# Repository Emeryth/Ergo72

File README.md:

# Ergo72

A redesigned ErgoDox keyboard PCB.
Check out [https://emeryth.net/ergo72-keyboard/](https://emeryth.net/ergo72-keyboard/) for more info.

Design features:

* Same key layout as the original Ergodox
* STM32 microcontroller (STM32F072)
* MCU in both halves allowing independent operation
* USB-C
* All components on PCB, no modules
* Extension header for OLED screen or anything else
* Single PCB for both hands
* QMK firmware supported

Basic acrylic case design included.

QMK firmware: [https://github.com/Emeryth/qmk_firmware/tree/ergo72](https://github.com/Emeryth/qmk_firmware/tree/ergo72)

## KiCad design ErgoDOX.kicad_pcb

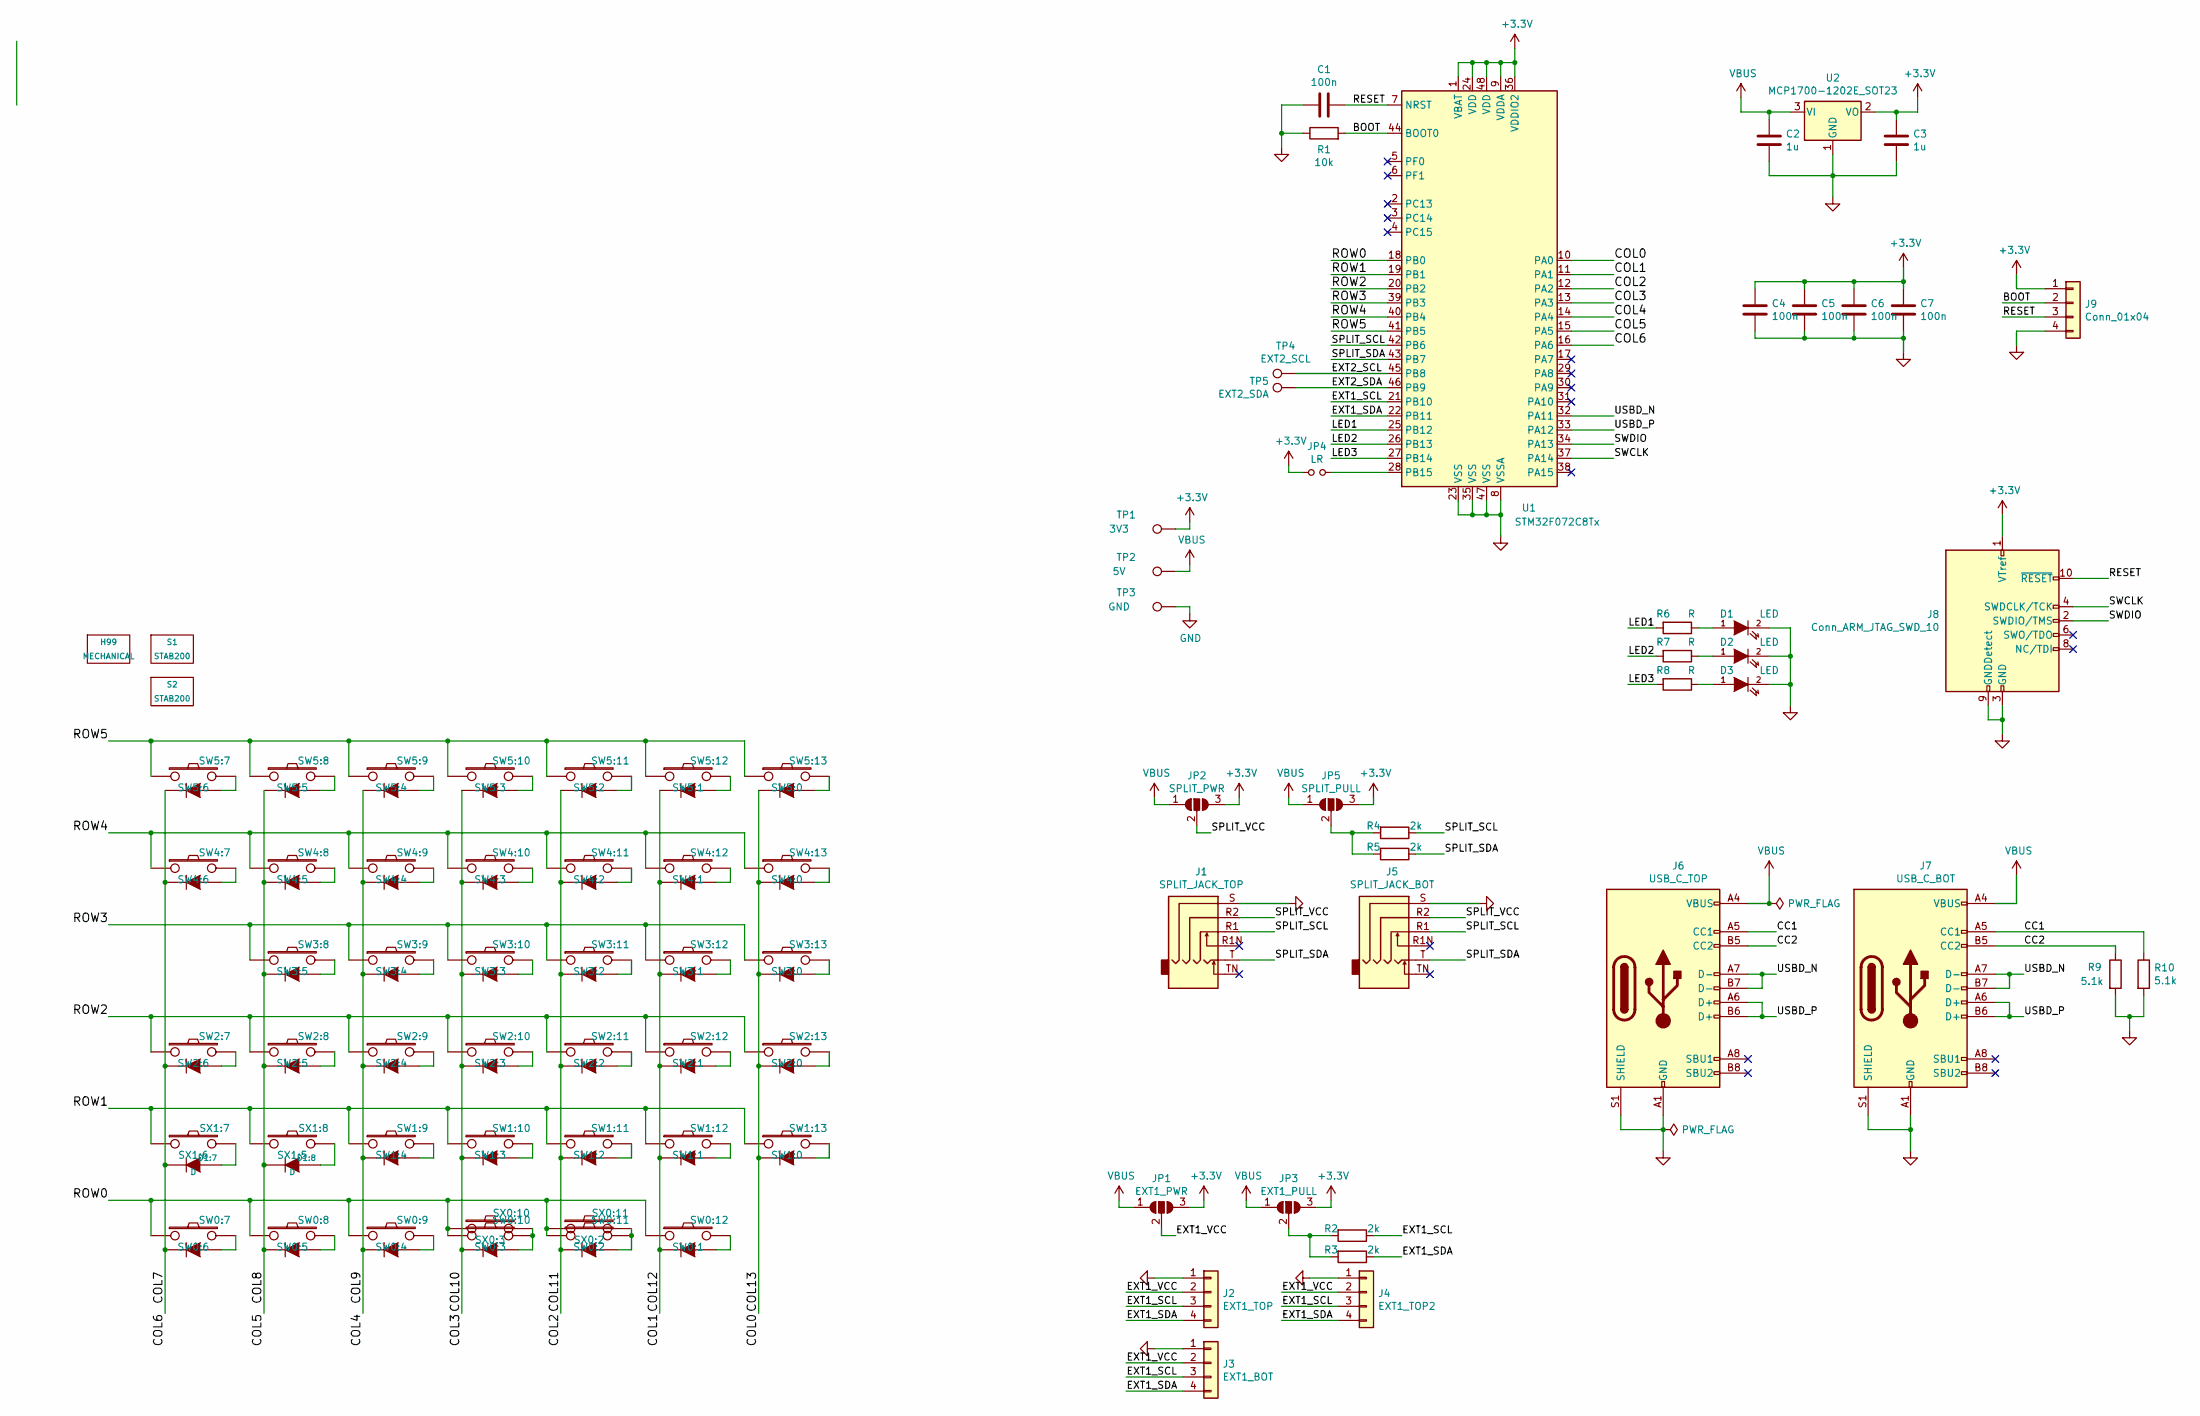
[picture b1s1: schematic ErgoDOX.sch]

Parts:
C1, C4, C5, C6, C7: 100n; C_0603_1608Metric
C2, C3: 1u; C_0805_2012Metric
D1, D2, D3: LED; LED_0603_1608Metric
D1:7, D1:8: D; DIODE
H99: MECHANICAL; ErgoDOXmech
J1: SPLIT_JACK_TOP; Jack_3.5mm_PJ31060-I_Horizontal
J2: EXT1_TOP; PinHeader_1x04_P2.54mm_Vertical
J3: EXT1_BOT; PinHeader_1x04_P2.54mm_Vertical
J4: EXT1_TOP2; Molex_PicoBlade_53047-0410_1x04_P1.25mm_Vertical
J5: SPLIT_JACK_BOT; Jack_3.5mm_PJ31060-I_Horizontal
J6: USB_C_TOP; USB_C_Receptacle_XKB_U262-16XN-4BVC11
J7: USB_C_BOT; USB_C_Receptacle_XKB_U262-16XN-4BVC11
J8: Conn_ARM_JTAG_SWD_10; PinHeader_2x05_P1.27mm_Vertical_SMD
J9: Conn_01x04; PinHeader_1x04_P2.54mm_Horizontal
JP1: EXT1_PWR; SolderJumper-3_P2.0mm_Open_TrianglePad1.0x1.5mm
JP2: SPLIT_PWR; SolderJumper-3_P2.0mm_Open_TrianglePad1.0x1.5mm
JP3: EXT1_PULL; SolderJumper-3_P2.0mm_Open_TrianglePad1.0x1.5mm
JP4: LR; SolderJumper-2_P1.3mm_Open_TrianglePad1.0x1.5mm
JP5: SPLIT_PULL; SolderJumper-3_P2.0mm_Open_TrianglePad1.0x1.5mm
R1: 10k; R_0603_1608Metric
R2, R3, R4, R5: 2k; R_0603_1608Metric
R6, R7, R8: R; R_0603_1608Metric
R9, R10: 5.1k; R_0603_1608Metric
S1, S2: STAB200
SW0:7: SW0:6; MX_FLIP_DIODE
SW0:8: SW0:5; MX_FLIP_DIODE
SW0:9: SW0:4; MX_FLIP_DIODE
SW0:10: SW0:3; MX_FLIP_DIODE
SW0:11: SW0:2; MX_FLIP_DIODE
SW0:12: SW0:1; MX_FLIP_DIODE
SW1:9: SW1:4; MX_FLIP_DIODE
SW1:10: SW1:3; MX_FLIP_DIODE
SW1:11: SW1:2; MX_FLIP_DIODE
SW1:12: SW1:1; MX_FLIP_DIODE
SW1:13: SW1:0; MX_FLIP_DIODE
SW2:7: SW2:6; MX_FLIP_DIODE
SW2:8: SW2:5; MX_FLIP_DIODE
SW2:9: SW2:4; MX_FLIP_DIODE
SW2:10: SW2:3; MX_FLIP_DIODE
SW2:11: SW2:2; MX_FLIP_DIODE
SW2:12: SW2:1; MX_FLIP_DIODE
SW2:13: SW2:0; MX_FLIP_XX
SW3:8: SW3:5; MX_FLIP_DIODE
SW3:9: SW3:4; MX_FLIP_DIODE
SW3:10: SW3:3; MX_FLIP_DIODE
SW3:11: SW3:2; MX_FLIP_DIODE
SW3:12: SW3:1; MX_FLIP_DIODE
SW3:13: SW3:0; MX_FLIP_XX
SW4:7: SW4:6; MX_FLIP_DIODE
SW4:8: SW4:5; MX_FLIP_DIODE
SW4:9: SW4:4; MX_FLIP_DIODE
SW4:10: SW4:3; MX_FLIP_DIODE
SW4:11: SW4:2; MX_FLIP_DIODE
SW4:12: SW4:1; MX_FLIP_DIODE
SW4:13: SW4:0; MX_FLIP_XX
SW5:7: SW5:6; MX_FLIP_DIODE
SW5:8: SW5:5; MX_FLIP_DIODE
SW5:9: SW5:4; MX_FLIP_DIODE
SW5:10: SW5:3; MX_FLIP_DIODE
SW5:11: SW5:2; MX_FLIP_DIODE
SW5:12: SW5:1; MX_FLIP_DIODE
SW5:13: SW5:0; MX_FLIP_XX
SX0:10: SX0:3; MX_FLIP
SX0:11: SX0:2; MX_FLIP
SX1:7: SX1:6; MX_FLIP
SX1:8: SX1:5; MX_FLIP
TP1: 3V3; TestPoint_Pad_D1.5mm
TP2: 5V; TestPoint_Pad_D1.5mm
TP3: GND; TestPoint_Pad_D1.5mm
TP4: EXT2_SCL; TestPoint_Pad_D1.5mm
TP5: EXT2_SDA; TestPoint_Pad_D1.5mm
U1: STM32F072C8Tx; LQFP-48_7x7mm_P0.5mm
U2: MCP1700-1202E_SOT23; SOT-23

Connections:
+3V3: C3.1, C4.1, C5.1, C6.1, C7.1, J8.1 (VTref), J9.1, JP1.3 (B), JP2.3 (B), JP3.3 (B), JP4.1, JP5.3 (B), TP1.1, U1.1 (VBAT), U1.9 (VDDA), U1.24 (VDD), U1.36 (VDDIO2), U1.48 (VDD), U2.2 (VO)
/BOOT: J9.2, R1.2, U1.44 (BOOT0)
/CC1: J6.A5 (CC1), J7.A5 (CC1), R10.1
/CC2: J6.B5 (CC2), J7.B5 (CC2), R9.1
/COL0: SW1:13.4 (K), SW2:13.4 (K), SW3:13.4 (K), SW4:13.4 (K), SW5:13.4 (K), U1.10 (PA0)
/COL1: SW0:12.4 (K), SW1:12.4 (K), SW2:12.4 (K), SW3:12.4 (K), SW4:12.4 (K), SW5:12.4 (K), U1.11 (PA1)
/COL4: SW0:9.4 (K), SW1:9.4 (K), SW2:9.4 (K), SW3:9.4 (K), SW4:9.4 (K), SW5:9.4 (K), U1.14 (PA4)
/COL5: D1:8.2 (K), SW0:8.4 (K), SW2:8.4 (K), SW3:8.4 (K), SW4:8.4 (K), SW5:8.4 (K), U1.15 (PA5)
/COL6: D1:7.2 (K), SW0:7.4 (K), SW2:7.4 (K), SW4:7.4 (K), SW5:7.4 (K), U1.16 (PA6)
/COL10: SW0:10.4 (K), SW1:10.4 (K), SW2:10.4 (K), SW3:10.4 (K), SW4:10.4 (K), SW5:10.4 (K), U1.13 (PA3)
/COL11: SW0:11.4 (K), SW1:11.4 (K), SW2:11.4 (K), SW3:11.4 (K), SW4:11.4 (K), SW5:11.4 (K), U1.12 (PA2)
/EXT1_SCL: J2.3, J3.3, J4.3, R2.1, U1.21 (PB10)
/EXT1_SDA: J2.4, J3.4, J4.4, R3.1, U1.22 (PB11)
/EXT1_VCC: J2.2, J3.2, J4.2, JP1.2 (C)
/EXT2_SCL: TP4.1, U1.45 (PB8)
/EXT2_SDA: TP5.1, U1.46 (PB9)
/LED1: R6.2, U1.25 (PB12)
/LED2: R7.2, U1.26 (PB13)
/LED3: R8.2, U1.27 (PB14)
/RESET: C1.1, J8.10 (~RESET~), J9.3, U1.7 (NRST)
/ROW0: SW0:7.1, SW0:8.1, SW0:9.1, SW0:10.1, SW0:11.1, SW0:12.1, SX0:10.1, SX0:11.1, U1.18 (PB0)
/ROW1: SW1:9.1, SW1:10.1, SW1:11.1, SW1:12.1, SW1:13.1, SX1:7.1, SX1:8.1, U1.19 (PB1)
/ROW2: SW2:7.1, SW2:8.1, SW2:9.1, SW2:10.1, SW2:11.1, SW2:12.1, SW2:13.1, U1.20 (PB2)
/ROW3: SW3:8.1, SW3:9.1, SW3:10.1, SW3:11.1, SW3:12.1, SW3:13.1, U1.39 (PB3)
/ROW4: SW4:7.1, SW4:8.1, SW4:9.1, SW4:10.1, SW4:11.1, SW4:12.1, SW4:13.1, U1.40 (PB4)
/ROW5: SW5:7.1, SW5:8.1, SW5:9.1, SW5:10.1, SW5:11.1, SW5:12.1, SW5:13.1, U1.41 (PB5)
/SPLIT_SCL: J1.R1, J5.R1, R4.1, U1.42 (PB6)
/SPLIT_SDA: J1.T, J5.T, R5.1, U1.43 (PB7)
/SPLIT_VCC: J1.R2, J5.R2, JP2.2 (C)
/SWCLK: J8.4 (SWDCLK/TCK), U1.37 (PA14)
/SWDIO: J8.2 (SWDIO/TMS), U1.34 (PA13)
/USBD_N: J6.A7 (D-), J6.B7 (D-), J7.A7 (D-), J7.B7 (D-), U1.32 (PA11)
/USBD_P: J6.A6 (D+), J6.B6 (D+), J7.A6 (D+), J7.B6 (D+), U1.33 (PA12)
GND: C1.2, C2.2, C3.2, C4.2, C5.2, C6.2, C7.2, D1.2 (K), D2.2 (K), D3.2 (K), J1.S, J2.1, J3.1, J4.1, J5.S, J6.A1 (GND), J6.A12 (GND), J6.B1 (GND), J6.B12 (GND), J6.S1 (SHIELD), J7.A1 (GND), J7.A12 (GND), J7.B1 (GND), J7.B12 (GND), J7.S1 (SHIELD), J8.3 (GND), J8.5 (GND), J8.9 (GNDDetect), J9.4, R1.1, R9.2, R10.2, TP3.1, U1.8 (VSSA), U1.23 (VSS), U1.35 (VSS), U1.47 (VSS), U2.1 (GND); also elsewhere on the board
unnamed: D1.1 (A), R6.1
unnamed: D1:7.1 (A), SX1:7.2
unnamed: D1:8.1 (A), SX1:8.2
unnamed: D2.1 (A), R7.1
unnamed: D3.1 (A), R8.1
unnamed: JP3.2 (C), R2.2, R3.2
unnamed: JP4.2, U1.28 (PB15)
unnamed: JP5.2 (C), R4.2, R5.2
unnamed: SW0:7.2, SW0:7.3 (A)
unnamed: SW0:8.2, SW0:8.3 (A)
unnamed: SW0:9.2, SW0:9.3 (A)
unnamed: SW0:10.2, SW0:10.3 (A), SX0:10.2
unnamed: SW0:11.2, SW0:11.3 (A), SX0:11.2
unnamed: SW0:12.2, SW0:12.3 (A)
unnamed: SW1:9.2, SW1:9.3 (A)
unnamed: SW1:10.2, SW1:10.3 (A)
unnamed: SW1:11.2, SW1:11.3 (A)
unnamed: SW1:12.2, SW1:12.3 (A)
unnamed: SW1:13.2, SW1:13.3 (A)
unnamed: SW2:7.2, SW2:7.3 (A)
unnamed: SW2:8.2, SW2:8.3 (A)
unnamed: SW2:9.2, SW2:9.3 (A)
unnamed: SW2:10.2, SW2:10.3 (A)
unnamed: SW2:11.2, SW2:11.3 (A)
unnamed: SW2:12.2, SW2:12.3 (A)
unnamed: SW2:13.2, SW2:13.3 (A)
unnamed: SW3:8.2, SW3:8.3 (A)
unnamed: SW3:9.2, SW3:9.3 (A)
unnamed: SW3:10.2, SW3:10.3 (A)
unnamed: SW3:11.2, SW3:11.3 (A)
unnamed: SW3:12.2, SW3:12.3 (A)
unnamed: SW3:13.2, SW3:13.3 (A)
unnamed: SW4:7.2, SW4:7.3 (A)
unnamed: SW4:8.2, SW4:8.3 (A)
unnamed: SW4:9.2, SW4:9.3 (A)
unnamed: SW4:10.2, SW4:10.3 (A)
unnamed: SW4:11.2, SW4:11.3 (A)
unnamed: SW4:12.2, SW4:12.3 (A)
unnamed: SW4:13.2, SW4:13.3 (A)
unnamed: SW5:7.2, SW5:7.3 (A)
unnamed: SW5:8.2, SW5:8.3 (A)
unnamed: SW5:9.2, SW5:9.3 (A)
unnamed: SW5:10.2, SW5:10.3 (A)
unnamed: SW5:11.2, SW5:11.3 (A)
unnamed: SW5:12.2, SW5:12.3 (A)
unnamed: SW5:13.2, SW5:13.3 (A)
VBUS: C2.1, J6.A4 (VBUS), J6.A9 (VBUS), J6.B4 (VBUS), J6.B9 (VBUS), J7.A4 (VBUS), J7.A9 (VBUS), J7.B4 (VBUS), J7.B9 (VBUS), JP1.1 (A), JP2.1 (A), JP3.1 (A), JP5.1 (A), TP2.1, U2.3 (VI)

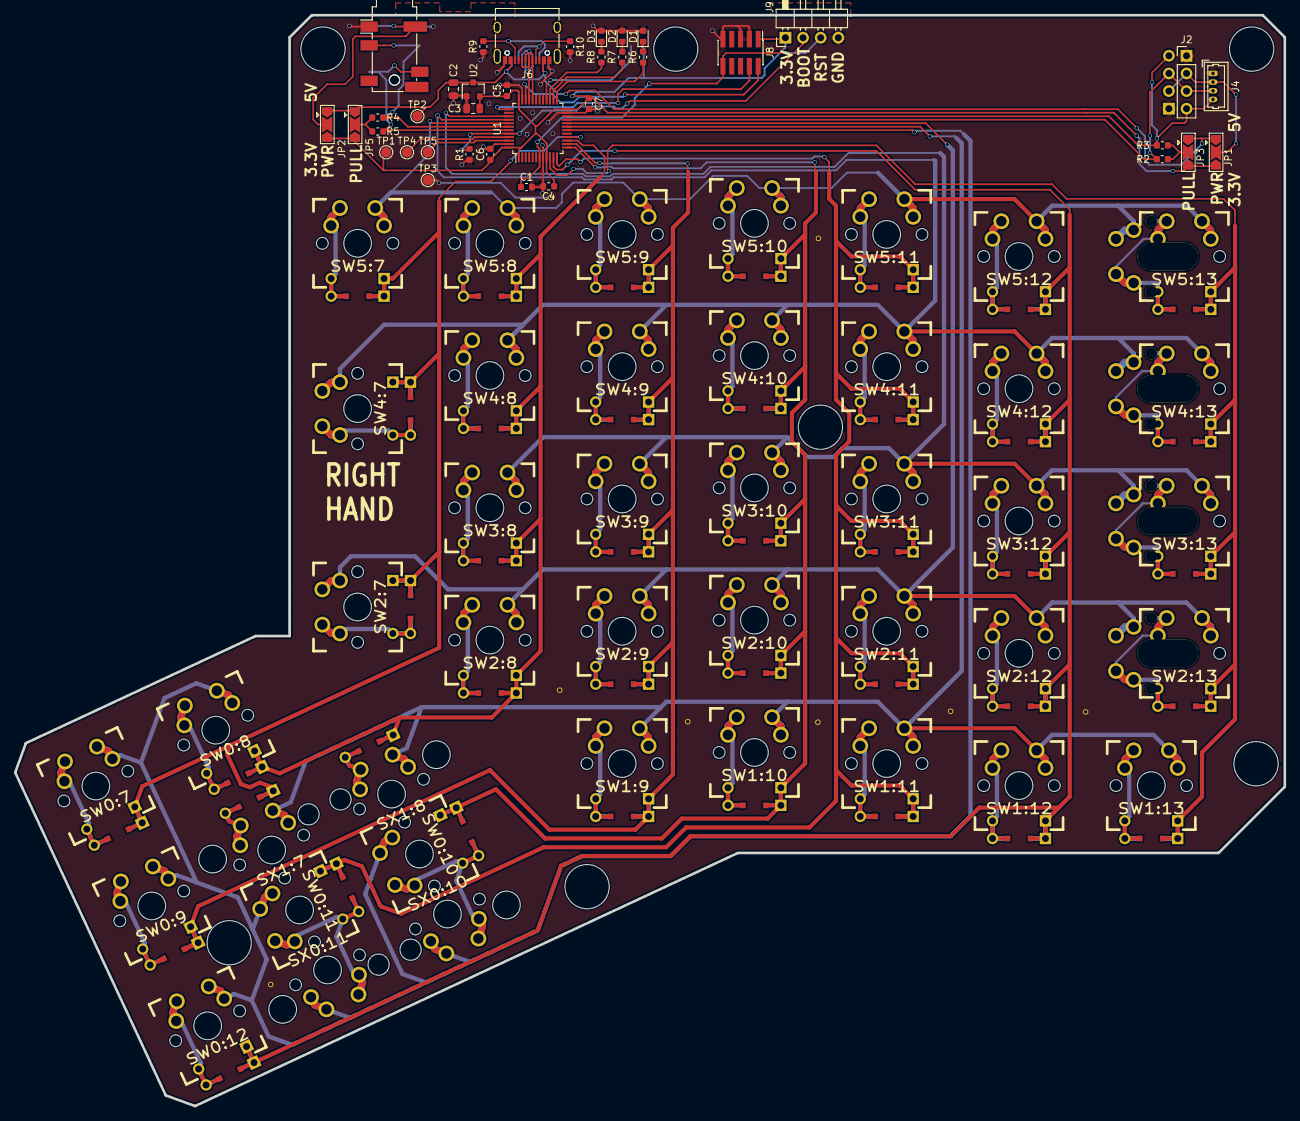
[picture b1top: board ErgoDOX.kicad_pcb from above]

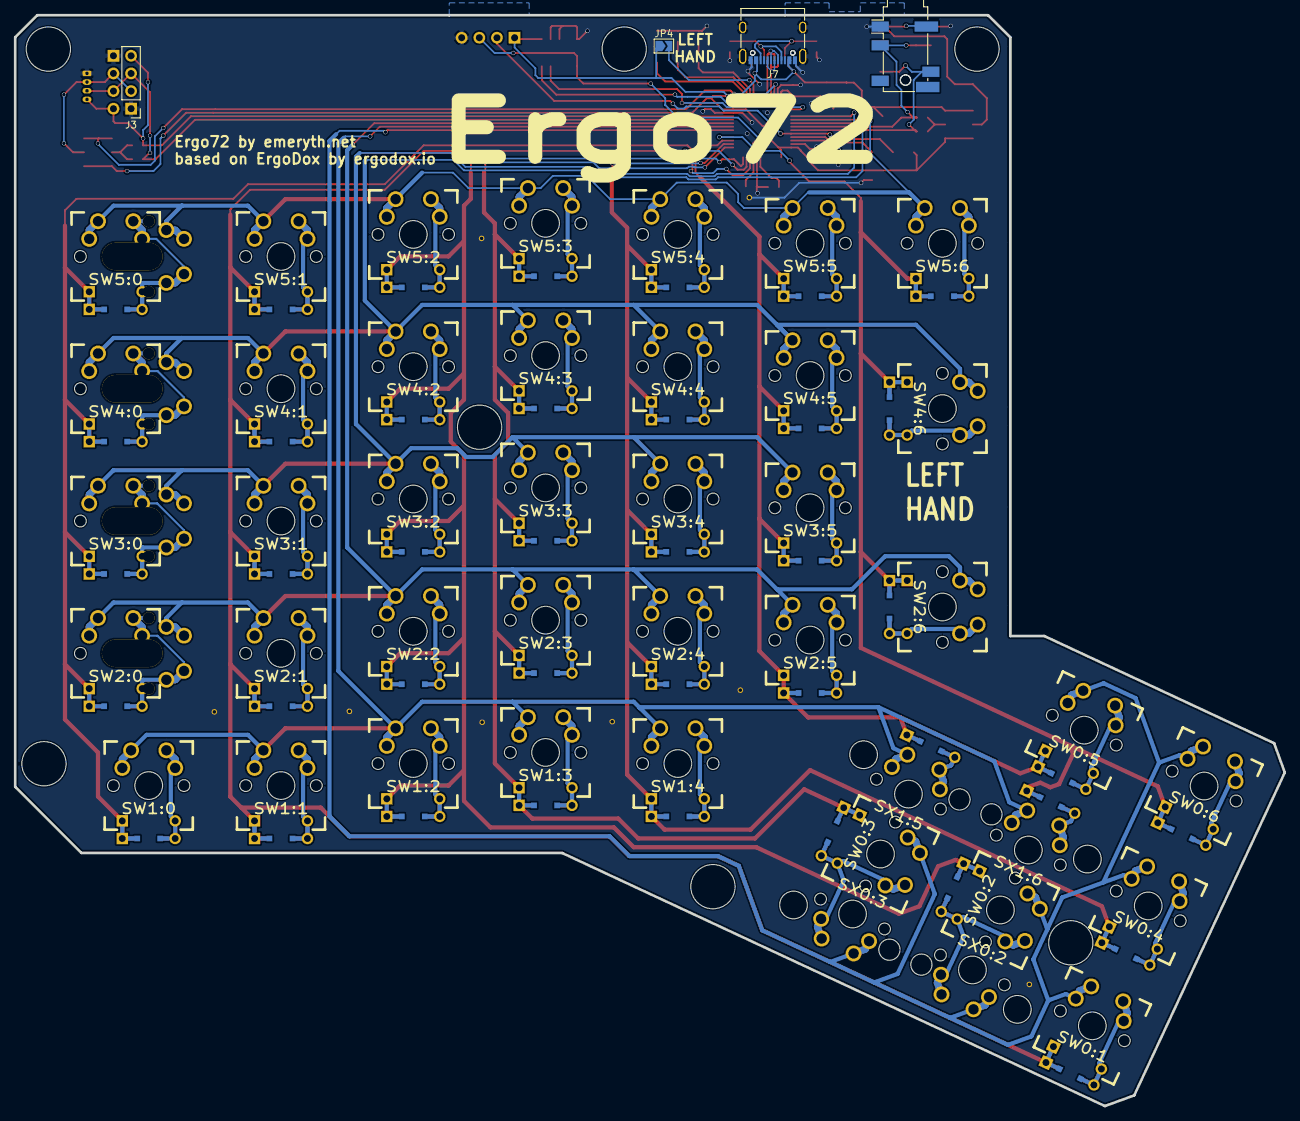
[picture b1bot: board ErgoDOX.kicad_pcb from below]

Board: 2 copper layers, 182.8 x 157.1 mm, 96 parts (4 on the bottom side), 81 nets.

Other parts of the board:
STITCHING_VIA: STITCHING_VIA
STITCHING_VIA#2, STITCHING_VIA#3, STITCHING_VIA#4, STITCHING_VIA#5, STITCHING_VIA#6, STITCHING_VIA#7, STITCHING_VIA#8: STITCHING_VIA

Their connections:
GND: STITCHING_VIA.GND, STITCHING_VIA#2.GND, STITCHING_VIA#3.GND, STITCHING_VIA#4.GND, STITCHING_VIA#5.GND, STITCHING_VIA#6.GND, STITCHING_VIA#7.GND, STITCHING_VIA#8.GND; also elsewhere on the board

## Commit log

2020-07-19 Initial commit.
2020-07-19 Assign footprints to old and new components.
2020-07-27 Routing done, needs review.
2020-08-02 Add testpoints and fix some stuff.
2020-09-01 Final version sent to the fab.
2020-09-01 Add documentation.
